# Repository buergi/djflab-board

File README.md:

# DJ FLAB Board

The DJ FLAB is a multi-room audio control board from Fablab München.

Multiple of these boards are connected to an ESP32, each providing a simple control interface for a single room.
It has a rotary encoder for controlling the volume and switching the audio source, as well as ten WS2812B LEDs for indication.

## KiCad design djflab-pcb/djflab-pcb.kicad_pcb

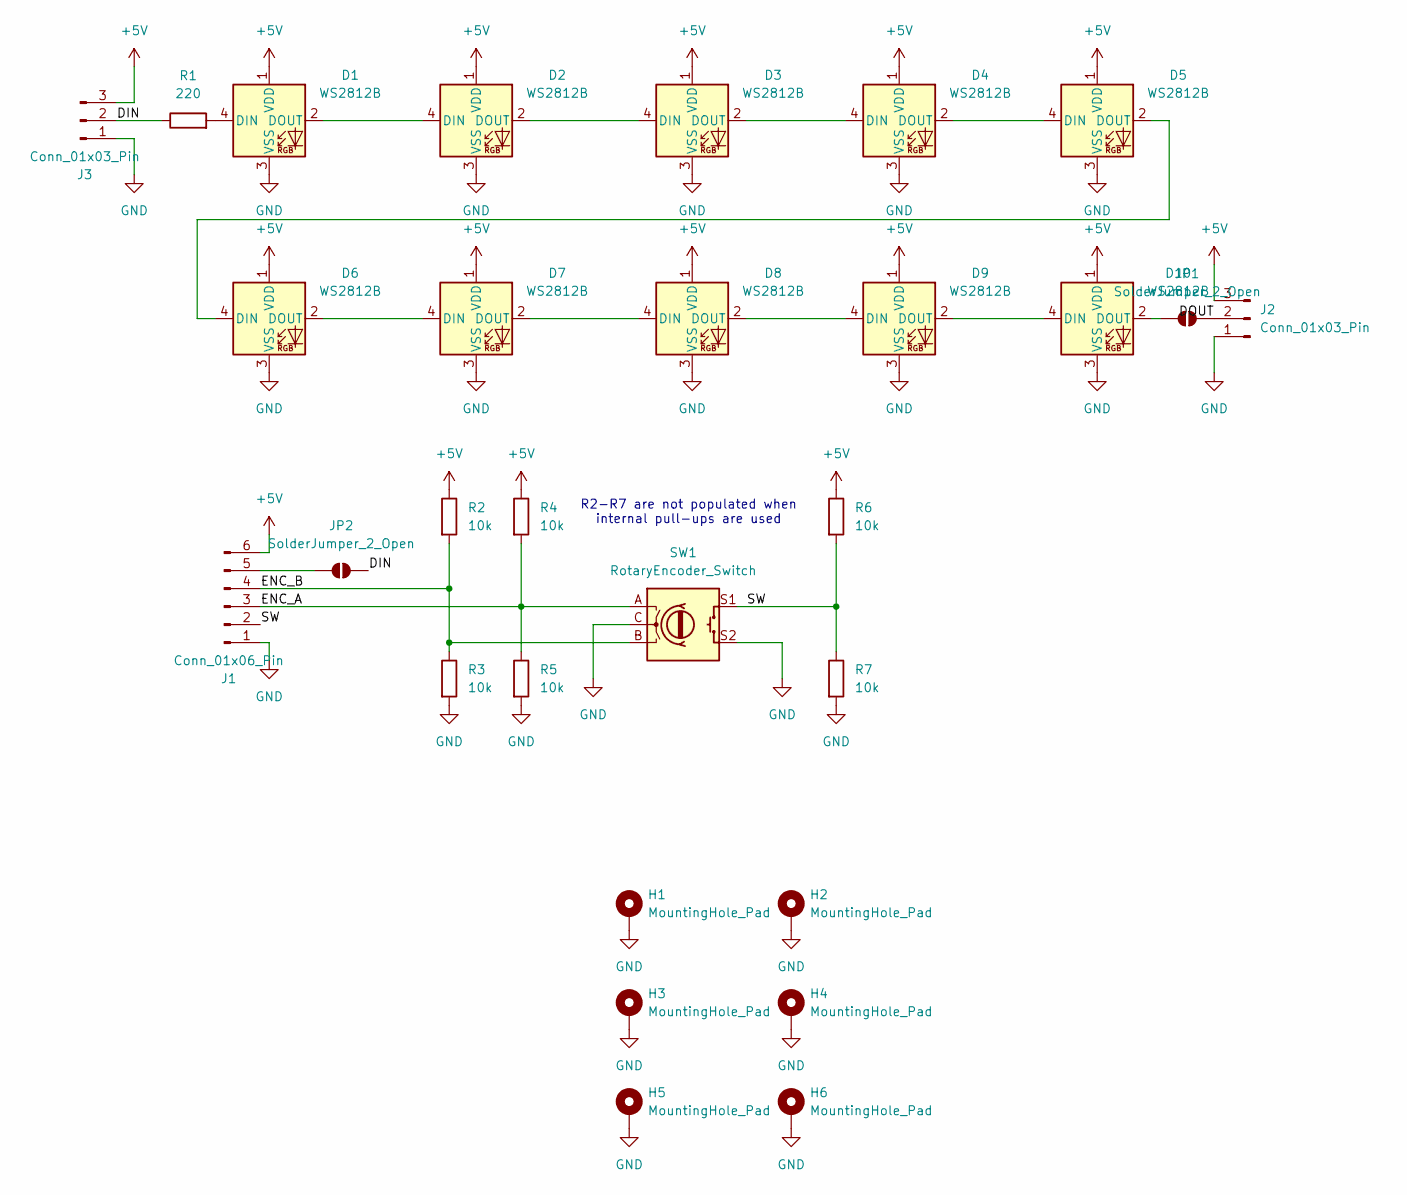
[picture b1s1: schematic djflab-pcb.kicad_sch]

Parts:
D1, D2, D3, D4, D5, D6, D7, D8, D9, D10: WS2812B; LED_WS2812B_PLCC4_5.0x5.0mm_P3.2mm
H1, H2, H3, H4: MountingHole_Pad; MountingHole_3.2mm_M3_Pad_Via
H5, H6: MountingHole_Pad; MountingHole_2.5mm_Pad_Via
J1: Conn_01x06_Pin; JST_XH_S6B-XH-A_1x06_P2.50mm_Horizontal
J2, J3: Conn_01x03_Pin; JST_XH_S3B-XH-A_1x03_P2.50mm_Horizontal
JP1, JP2: SolderJumper_2_Open; SolderJumper-2_P1.3mm_Open_RoundedPad1.0x1.5mm
R1: 220; R_0805_2012Metric_Pad1.20x1.40mm_HandSolder
R2, R3, R4, R5, R6, R7: 10k; R_0805_2012Metric_Pad1.20x1.40mm_HandSolder
SW1: RotaryEncoder_Switch; RotaryEncoder_Bourns_Vertical_PEC12R-3x17F-Sxxxx

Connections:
+5V: D1.1 (VDD), D2.1 (VDD), D3.1 (VDD), D4.1 (VDD), D5.1 (VDD), D6.1 (VDD), D7.1 (VDD), D8.1 (VDD), D9.1 (VDD), D10.1 (VDD), J1.6, J2.3, J3.3, R2.1, R4.1, R6.1
/DIN: J3.2, JP2.2 (B), R1.1
/ENC_A: J1.3, R4.2, R5.1, SW1.A
/ENC_B: J1.4, R2.2, R3.1, SW1.B
/SW: J1.2, R6.2, R7.1, SW1.S1
GND: D1.3 (VSS), D2.3 (VSS), D3.3 (VSS), D4.3 (VSS), D5.3 (VSS), D6.3 (VSS), D7.3 (VSS), D8.3 (VSS), D9.3 (VSS), D10.3 (VSS), H1.1, H2.1, H3.1, H4.1, H5.1, H6.1, J1.1, J2.1, J3.1, R3.2, R5.2, R7.2, SW1.C, SW1.S2
unnamed: D1.4 (DIN), R1.2
unnamed: D1.2 (DOUT), D2.4 (DIN)
unnamed: D2.2 (DOUT), D3.4 (DIN)
unnamed: D3.2 (DOUT), D4.4 (DIN)
unnamed: D4.2 (DOUT), D5.4 (DIN)
unnamed: D5.2 (DOUT), D6.4 (DIN)
unnamed: D6.2 (DOUT), D7.4 (DIN)
unnamed: D7.2 (DOUT), D8.4 (DIN)
unnamed: D8.2 (DOUT), D9.4 (DIN)
unnamed: D9.2 (DOUT), D10.4 (DIN)
unnamed: D10.2 (DOUT), JP1.1 (A)
unnamed: J1.5, JP2.1 (A)
unnamed: J2.2, JP1.2 (B)

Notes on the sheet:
R2-R7 are not populated when internal pull-ups are used

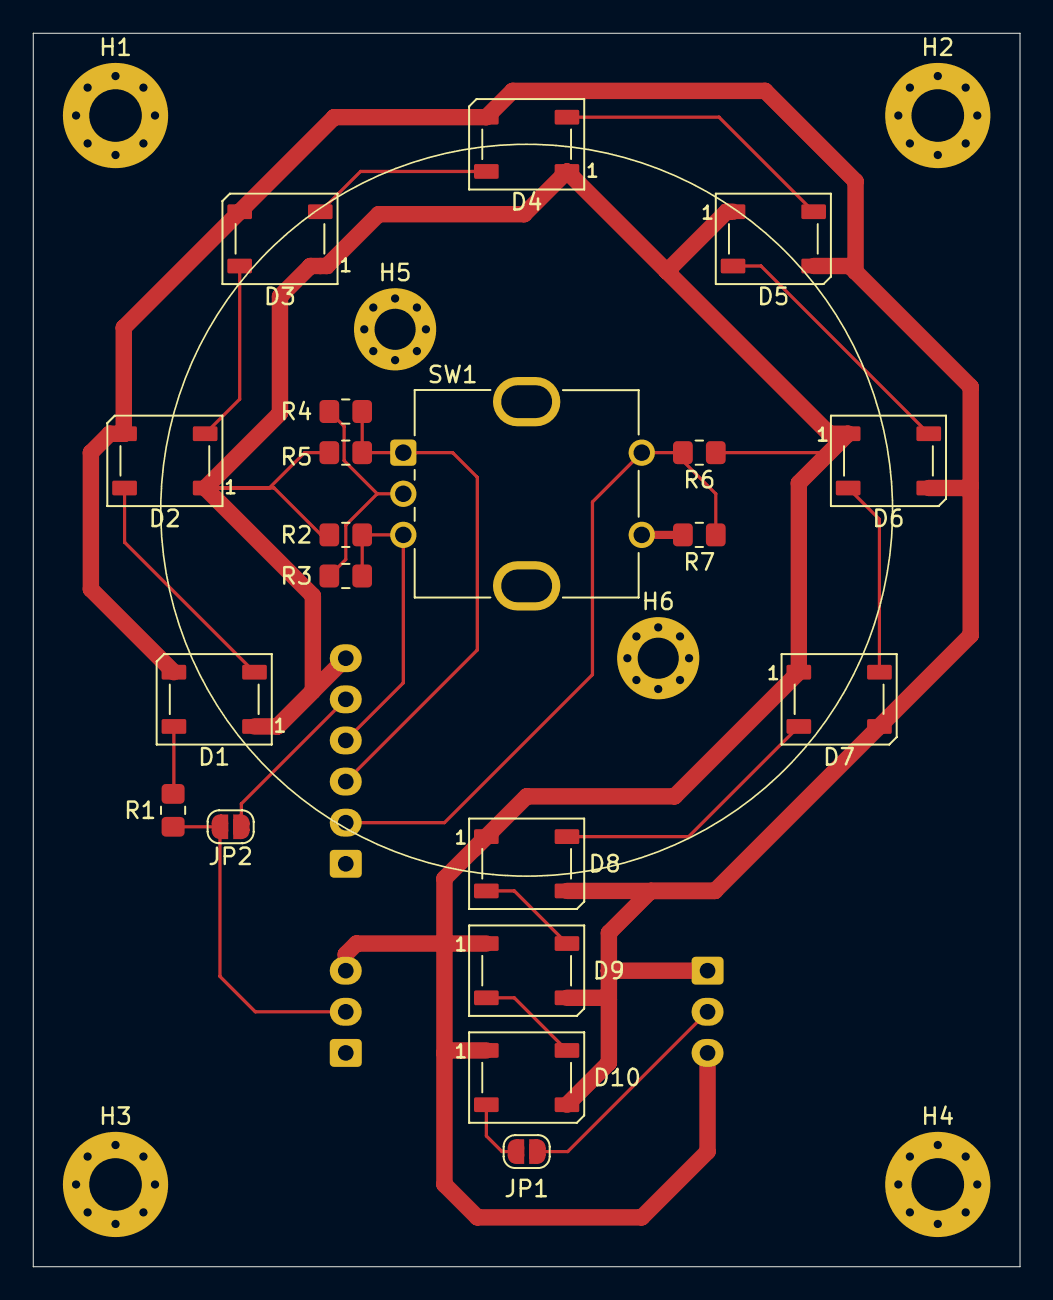
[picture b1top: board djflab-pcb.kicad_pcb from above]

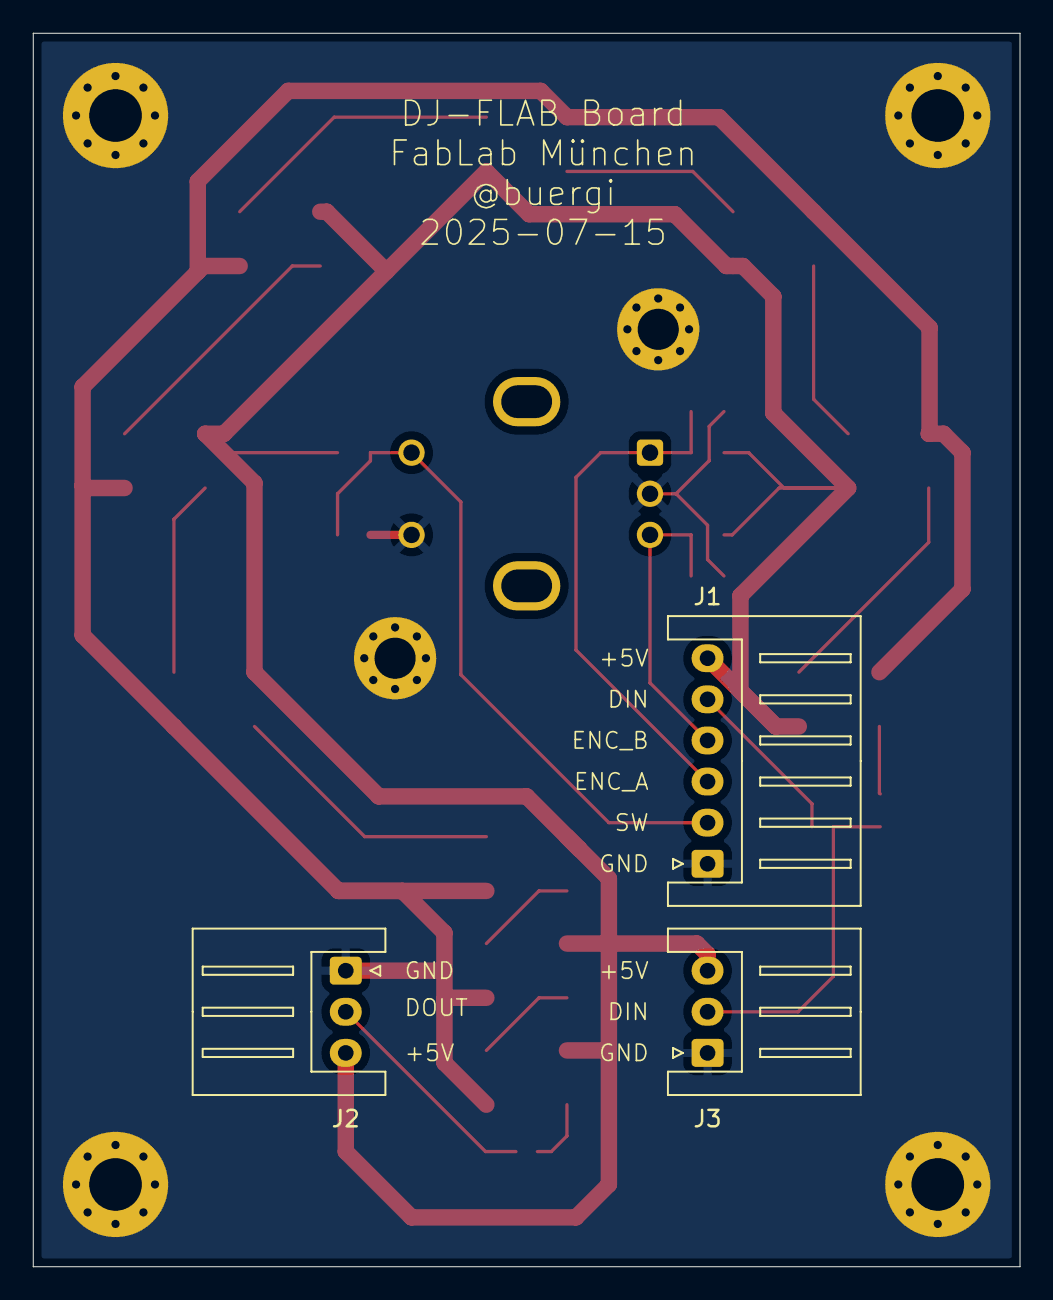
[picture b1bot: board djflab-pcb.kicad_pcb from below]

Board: 2 copper layers, 60.0 x 75.0 mm, 29 parts (3 on the bottom side), 19 nets.

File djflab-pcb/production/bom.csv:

Designator,Footprint,Quantity,Value,LCSC Part #
"D1, D10, D2, D3, D4, D5, D6, D7, D8, D9",LED_WS2812B_PLCC4_5.0x5.0mm_P3.2mm,10,WS2812B,
J1,JST_XH_S6B-XH-A_1x06_P2.50mm_Horizontal,1,Conn_01x06_Pin,
"J2, J3",JST_XH_S3B-XH-A_1x03_P2.50mm_Horizontal,2,Conn_01x03_Pin,
R1,0805,1,220,
"R2, R3, R4, R5, R6, R7",0805,6,10k,
SW1,RotaryEncoder_Bourns_Vertical_PEC12R-3x17F-Sxxxx,1,RotaryEncoder_Switch,
